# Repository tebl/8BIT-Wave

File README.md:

# 8BIT Wave
8BIT Wave is a project I started in order to build a digital cassette deck for my old 8-bit retro computers, my starting point was the schematic provided as part of the [DigiWavuino](https://github.com/rickyelqasem/DigiWavuino) project by Ricky ElQasem though it's more or less grown towards being its own thing since then. Later versions also support the [Maxduino](https://github.com/rcmolina/MaxDuino_v1.66)-firmware (includes tzxduino and arduitape functionality), that way I can use it with most - if not all of my vintage computers using one device (refer to maxduino documentation). Anyway, enough of all that - here is a picture of the device loading a game on ZX Spectrum:

One of my goals with the project has been to build the device I always wanted, the idea was to have something that looked like a cassette tape yet had all the functionality of maxduino and similar firmware. There is a firmware in the software-directory of this repository, but that was more a way of playing around with the Arduino without ever intending to finish it (it is only there in case someone wants to study and laugh at my cut-and-paste style of coding).

So my major contribution for this projection, to the world in general, is in the form of the three PCBs and some added amplifier options not found on any of the other open tzxduino clones I've looked at. The other goal, apart from looking cool was having a case without actually fixing my 3d-printer so for that reason the project also includes a backplate - this allows the user to avoid having to touch bare electronics when they handle it.

It is my belief that this project can be put together by anyone with moderate skills at soldering together components, but take care that you read through all of the documentation provided and not just start somewhere in the middle. All the components I've used are from chinese vendors such as AliExpress, banggood and ebay so the descriptions will reflect this (none of those sites have consistent part descriptions, so treat the parts list as general search terms and try to match them to pictures).

Further details will be available as part of the documentation for each of the [modules](#2-modules), see below for links.

## 1> Project status
There will always be things to do and polish, but at the current state it is an open design that can be used with the [MaxDuino](https://github.com/rcmolina/MaxDuino_v1.54). Note that different computers have that special sweet spot, so that you will need to do some tweaking in order to find what works best with your specific setup. 

## 2> Modules
The project has been split into several modules, these will be stacked together to a complete player. Faceplates and backplates can be considered optional, but normally you would only need one of each (some variants will be added later to match various displays so check out the description for each module before you commit).

| Module    |  | Order |
| --------- | ---------- | ----- |
| [8BitWave Module](https://github.com/tebl/8BIT-Wave/tree/master/8bitWave%20Module) | required | [PCBWay](https://www.pcbway.com/project/shareproject/8BitWave_Module.html) |
| [8BitWave Faceplate A1](https://github.com/tebl/8BIT-Wave/tree/master/8bitWave%20Faceplate%20A1) | optional | |
| [8BitWave Faceplate A2](https://github.com/tebl/8BIT-Wave/tree/master/8bitWave%20Faceplate%20A2) | recommended | [PCBWay](https://www.pcbway.com/project/shareproject/8BitWave_Faceplate.html) |
| [8BitWave Backplate](https://github.com/tebl/8BIT-Wave/tree/master/8bitWave%20Backplate) | optional | [PCBWay](https://www.pcbway.com/project/shareproject/8BitWave_Backplate.html) |

I'm using PCBway because I get a discount for every PCB ordered via them, so if you want to support this project then that is the way to do it. For other fabrication houses you would normally need to do is zip-up the contents of the export directory for each module and hand them those files (these are what is known as Gerber files). Note that the latest Gerber files may contain changes not yet tested by me, so if you want the ones I've tested then checkout my [PCBway shared projects](https://www.pcbway.com/project/shareproject/?tag=8BIT-Wave) relating to this project.

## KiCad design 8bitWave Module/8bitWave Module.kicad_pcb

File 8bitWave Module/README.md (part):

# 8BIT Wave Module

The 8BIT Wave module is the main heart of the project, it contains most of the active components found within the project. Building the module requires that you take some time to consider to which options you require, some in the case of the chosen amplifier are mutually exclusive and they both have their plusses and minuses. If you're still in the process of ordering components, skip to the BOM section of the document and start there - note that other modules such has the faceplate will have their documents detailing their construction and part specifications.

- 1> [Building the module](#1-building-the-module)
  - 1.1> [Installing common components](#11-installing-common-components)
  - 1.2> [Installing low-pass filter](#12-installing-low-pass-filter)
  - 1.3> [Installing amplifier](#13-installing-amplifier)
    - [1.3.1> LM386 amplifier option](#131-lm386-amplifier-option)
    - [1.3.2> GF1002 amplifier option](#132-gf1002-amplifier-option)
- 2> [Schematic](#2-schematic)
- 3> [BOM](#3-bom)
  - 3.1> [Common components](#31-common-components)
  - 3.2> [LM386 (amplifier)](#32-lm386-amplifier)
  - 3.3> [GF1002 (amplifier)](#33-gf1002-amplifier)
  - 3.4> [Low-pass filter](#34-low-pass-filter)

## 1> Building the module
So you've decided that you want the 8BIT Wave in your life, a bold choice and might I go so far as smile that someone took the time to build something I designed. The first step before breaking out the soldering iron, you can't use a glue-gun for this unless you do some extreme overclocking on the thing, is going through and ordering all the little bits you'll need. This should all be detailed inside the section later in this document, called the [BOM](#3-bom) (bill of manufacturing). Note that you will however have to make some decisions about a few of the options, mainly the amplification used and whether you want to install components for the low-pass filter. Read each section carefully before you commit to something, components are always harder to desolder than it is to solder them into place (when in doubt and have the extra PCB, just build another one - twice the solder fumes for just about the same price).

Got everything needed? Awesome. Break out your soldering iron, add some water to the sponge and start soldering at a reasonably controlled temperature. I have my iron set around 340 degrees Celsius, in Fahrenheit that would be too cold to accomplish much [cue laugh track]!

Continue by following sections [1.1](#11-installing-common-components) to install common common components, [1.2](#12-installing-low-pass-filter) to install a low-pass filter (if needed) and finally the amplifier option you require by following on in section [1.3](#13-installing-amplifier).

- [1.1> Installing common components](#11-installing-common-components)
- [1.2> Installing low-pass filter](#12-installing-low-pass-filter)
- [1.3> Installing amplifier](#13-installing-amplifier)

When all that is done, including any work that needs to be done on the faceplate/backplate you should now be able to put the entire thing together. What I recommend is that you get one of those M3 nylon hex standoff kits, that way you have a bunch available of various lengths that you can use while you build the completed solution. The ones I've between the faceplate and the main module are 12mm long, then whatever is the shortest I have available between backplate and the main module.

A minimum height build is shown below, here it is running Maxduino and the total height is around 26mm which is pretty good compared to most cased designs.

### 1.1> Installing common components
Solder parts specified in [common components](#31-common-components) into place, but take note that depending on the build you're going for you'll probably need to use some hex standoffs between this module and the faceplate - the ones I'm using is 12mm tall. You might get away with substituting the long pin headers with the regular ones if you opt to install the Arduino directly without anything in between, but doing so requires you to do some dry-fitting along the way to make sure nothing becomes too short (a long pin can be cut, a short one can be heated and pushed a bit through to make up for it).

The modules that can be installed directly on the board is shown above, both of them usually come with pin headers already attached - we'll deal with those along the way. The display you can probably put aside as you've most likely opted for installing it on one of my beautiful faceplates instead (I can't blame you, that was really what this project was all about). If you however do not want the faceplate (why though?), make sure you install the display as the last thing you ever do - otherwise you'll have problems installing components below it (add some electrical tape between the modules to avoid accidentally shorting things).

The MicroSD Card Adapter will come with right-angle header attached to it, just straighten them using some pliers. Add some double-sided tape to the top of the MicroSD-slot, turn it upside down and solder it into place on the module.

### 1.2> Installing low-pass filter
Solder in the parts for the [low-pass filter](#34-low-pass-filter), unless you know you'll need them. They have been shown to make programs easier to load on the MSX-line of computers though it's the only place I think it is needed. If you chose to skip the installation, feel free to install a wire-link across J5 pins 1-2. With the filter installed, add some dual-row header pins to J5 - disable the filter by placing a jumper across pins 1-2 as before. When enabling the feature you'll need to remove this jumper, instead add jumpers across pins 3-4 and 5-6. 

### 1.3> Installing amplifier
With this step out of the way, we're ready to install one of the amplifier options, the easiest one is simply using the module without an amplifier - install jumpers across J7 pins 1-2 as well as 11-12 to use the output directly (this will also allow you to bypass an installed amplifier). The following sections assume that you've chosen to install either LM386 or GF1002 amplifier, they operate at different voltages and should not be installed in the same system.

- [1.3.1> LM386 amplifier option](#131-lm386-amplifier-option)
- [1.3.2> GF1002 amplifier option](#132-gf1002-amplifier-option)

#### 1.3.1 LM386 amplifier option
Using the classic LM386 amplifier is more or less the goto choice for any amateur hardware tinkerer, thinking mostly about me here - you're probably awesome so don't worry about it! It is also a common option found on other tzxduino boards, but note that the module really requires 9v to function properly with a few vintage systems, even just specific revisions may require this as opposed to the 5v provided by the Arduino.

Try it out, it might work perfectly at 5v too so you need to try out which works best for the systems you have. If you explicitly don't want to add a 9v power supply into the mix, the [GF1002 amplifier](#132-gf1002-amplifier-option) is a different option that has been designed to operate at 5v.

Still here? 9v center positive power supply it is then. Install components specified in the [BOM](#32-lm386-amplifier). Link pins JP6 pins 2-3 and make a checkmark in the 9v checkbox on the back of the module, this is here so you don't accidentally connect the wrong voltage to the module. Note that with JP6 in the wrong position, this will more than likely fry most of the components on the board - do it right or watch it burn (probably a lot less spectacular than that)! Refer to the picture below if in doubt.

Most components can be installed as shown, but in order to keep the spacing between the module and faceplate as little as possible (12mm by my count) you'll need to install some of the components on their side - the capactitors especially can be tall, by putting them on the side you have a bit more room to work with. The same goes for the volume control, this is the same 10k bourns 3296w potentiometer most usually have in their parts bin - what I've done is simply mount it on the side by bending the pins. It is then anchored to the board by using some leftover wire-cuttings from one of the LEDs.

As mentioned before, J7 configures the amplification used by the system. You can use jumper pins 1-2 to bypass the LM386 if needed, but since you're here you probably want to enable the thing - this is done by adding jumpers across 5-6 instead (assuming you still have a jumper in place across pins 11-12).

#### 1.3.2 GF1002 amplifier option
The GF1002 amplifier module, based on PAM8403 module, is a stereo amplifier that's been designed for use with 5v (LM386 requires 9v) power sources so it is a good match for the *8BIT Wave*. For the most part it is easy to install, but feel free to refer to section [3.3](#33-gf1002-amplifier) for a list of parts needed and install them as you see fit - a picture of the completed module can be seen below.

The most important thing to remember when installing it is that the audio jacks must be in place before you attempt to install the GF1002, mainly because they will be partially covered by the module. You will also need to have the module in part recessed into the cutout on the PCB, this was done so that the overall thickness of all the PCBs can be kept to a minimum. Use long pin headers, break them into sections and use those when soldering it in at the correct height - ideally it'll be resting comfortably on top of the 3.5mm audio jack.

Power can also be supplied directly by plugging in a 5v DC (center positive) power supply into the barrel connector, this require JP6 to have a wire-ling across pins 1-2. These components are listed as optional (in parenthesis), so make a checkmark in the corresponding box on the back of the module board to mark it as such.

As mentioned before, J7 configures the amplification used by the system. You can use jumper pins 1-2 to bypass the GF1002 if needed, but since you're here you probably want to enable the thing - this is done by adding jumpers across J7 pins 7-8 as well as pins 9-10. Note that no other J7 pins should be jumpered here, the GF1002 needs to have it's own ground and shorting it using pins 11-12 will cause it to overheat and shut down.

# 2> Schematic
The supplied KiCad files should be sufficient as both a schematic and as a  starting point for ordering PCBs (basically you could just zip the contents of the export folder and upload that on a fabrication site), the schematic is also available in [PDF-format](https://github.com/tebl/8BIT-Wave/tree/master/documentation/schematic) found within the schematics-part of the [documentation](https://github.com/tebl/8BIT-Wave/tree/master/documentation).

# 3> BOM
Most parts should be easy to get a hold of from your favourite local electronic component shop, but given that I don't have access to such shops where I live so everything was based on whatever I could get cheapest from eBay/AliExpress (free shipping, plan on waiting 3-4 weeks for delivery though).

As described in the section *building the module*, the BOM will also need to be divided into various sections depending on the chosen build - these difference between these is the choice of amplifier installed. Common components are needed for all of them, refer to the rest for a different choice - do note however that the option of no amplification similar to what is found on the tzxduino compact is also an option. Components listen in parenthesis is to be considered optional, some of them will be obsolete when using a faceplate (only one display needed).

# 3.1> Common components
These are the components that will be required on all variants of the 8BIT Wave, do note that depending on options chosen the design may be simplified by doing part substitutions. In particular the long pin can be substituted by ordinary pin headers if all components are soldered directly to the PCB without using sockets, LM386 or no amplifier etc. Refer to the following [picture](https://github.com/tebl/8BIT-Wave/raw/master/gallery/2020-02-22%2000.55.06.jpg) if you're wondering what the MicroSD Card Adapter module looks like.

| Reference    | Item                                                 | Count |
| ------------ | ---------------------------------------------------- | ----- |
| PCB          | Fabricate using Gerber files                         |     1 |
| A1           | Arduino Nano or Every                                |     1 |
| A2           | MicroSD Card Adapter for Arduino                     |     1 |
| C10          | 100uF 16V electrolytic capacitor                     |     1 |
| D1,D2 **     | 5mm LED                                              |    (2)|
| IC1          | SSD1306 I2C OLED 128x64 (0.96")                      |    (1)|
| J1           | PJ-210 2.5mm audio socket                            |    (1)|
| J2           | PJ-307 3.5mm audio socket (5 pin)                    |     1 |
| J6,JP5       | 3 pin straight header (long pins)                    |     2 |
| J3           | 7 pin header (long pins)                             |     1 |
| J5 *         | 2x3 straight pin header                              |     1 |
| J7           | 2x7 straight dual row pin header                     |     1 |
| R6,R7 **     | 330 Ohm resistor                                     |    (2)|
| R8,R9 ***    | 4k7 (4700) Ohm resistor                              |    (2)|
| SW1-SW5      | 6x6x5mm right-angle momentary button                 |     5 |
| Jumpers      | Pin header jumper caps                               |     5 |

*) This is used to enable/disable the low-pass filter, if you don't need or want to install the components listed in section 3.4 you can just install a wire link across pins 1-2 to permanently bypass it.

**) These components are only on the 8BIT-Wave, the Maxduino firmware does not support them so they are listed as optional.

***) These are I2C pull-ups, these are normally needed as the OLED-displays tend to already come with those installed there. Only install if you've verified that this is the issue.

# 3.2> LM386 (amplifier)
The classic option for amplifying the audio signal on a tzxduino. No amplification at all is also an option that can be considered, but with some systems and even revisions of specific systems there will be different audio requirements that will require active amplification (see 3.3 for a different option).

Note that the LM386 really needs more than 5v to function properly, so you'll need to power the system with a 9v DC (center positive) using the barrel connector. This requires JP6 to have a wire-link between pins 2-3, pins 1-2 should only be linked if you mean to use a different amplification option and a 5v DC (center positive) power supply. Make a checkmark on the 9v section on the back of the board.

| Reference    | Item                                                 | Count |
| ------------ | ---------------------------------------------------- | ----- |
| C5           | 100nF ceramic capacitor (5mm)                        |     1 |
| C6,C8        | 10uF 16V electrolytic capacitor                      |     2 |
| C7           | 100uF 16V electrolytic capacitor                     |     1 |
| C9           | 47nF ceramic capacitor (5mm)                         |     1 |
| C11          | 220uF 16V electrolytic capacitor                     |     1 |
| D3           | 1n4001 diode (DO-41)                                 |     1 |
| J4           | 5.5mm x 2.1mm barrel connector (PCB mount)           |     1 |
| R5           | 10 Ohm resistor                                      |     1 |
| RV2          | Bourns 3296W 10k ohm potentiometer                   |     1 |
| JP1,JP6      | 3 pin straight header with jumper                    |     2 |
| JP4          | 2 pin straight header with jumper                    |     1 |

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
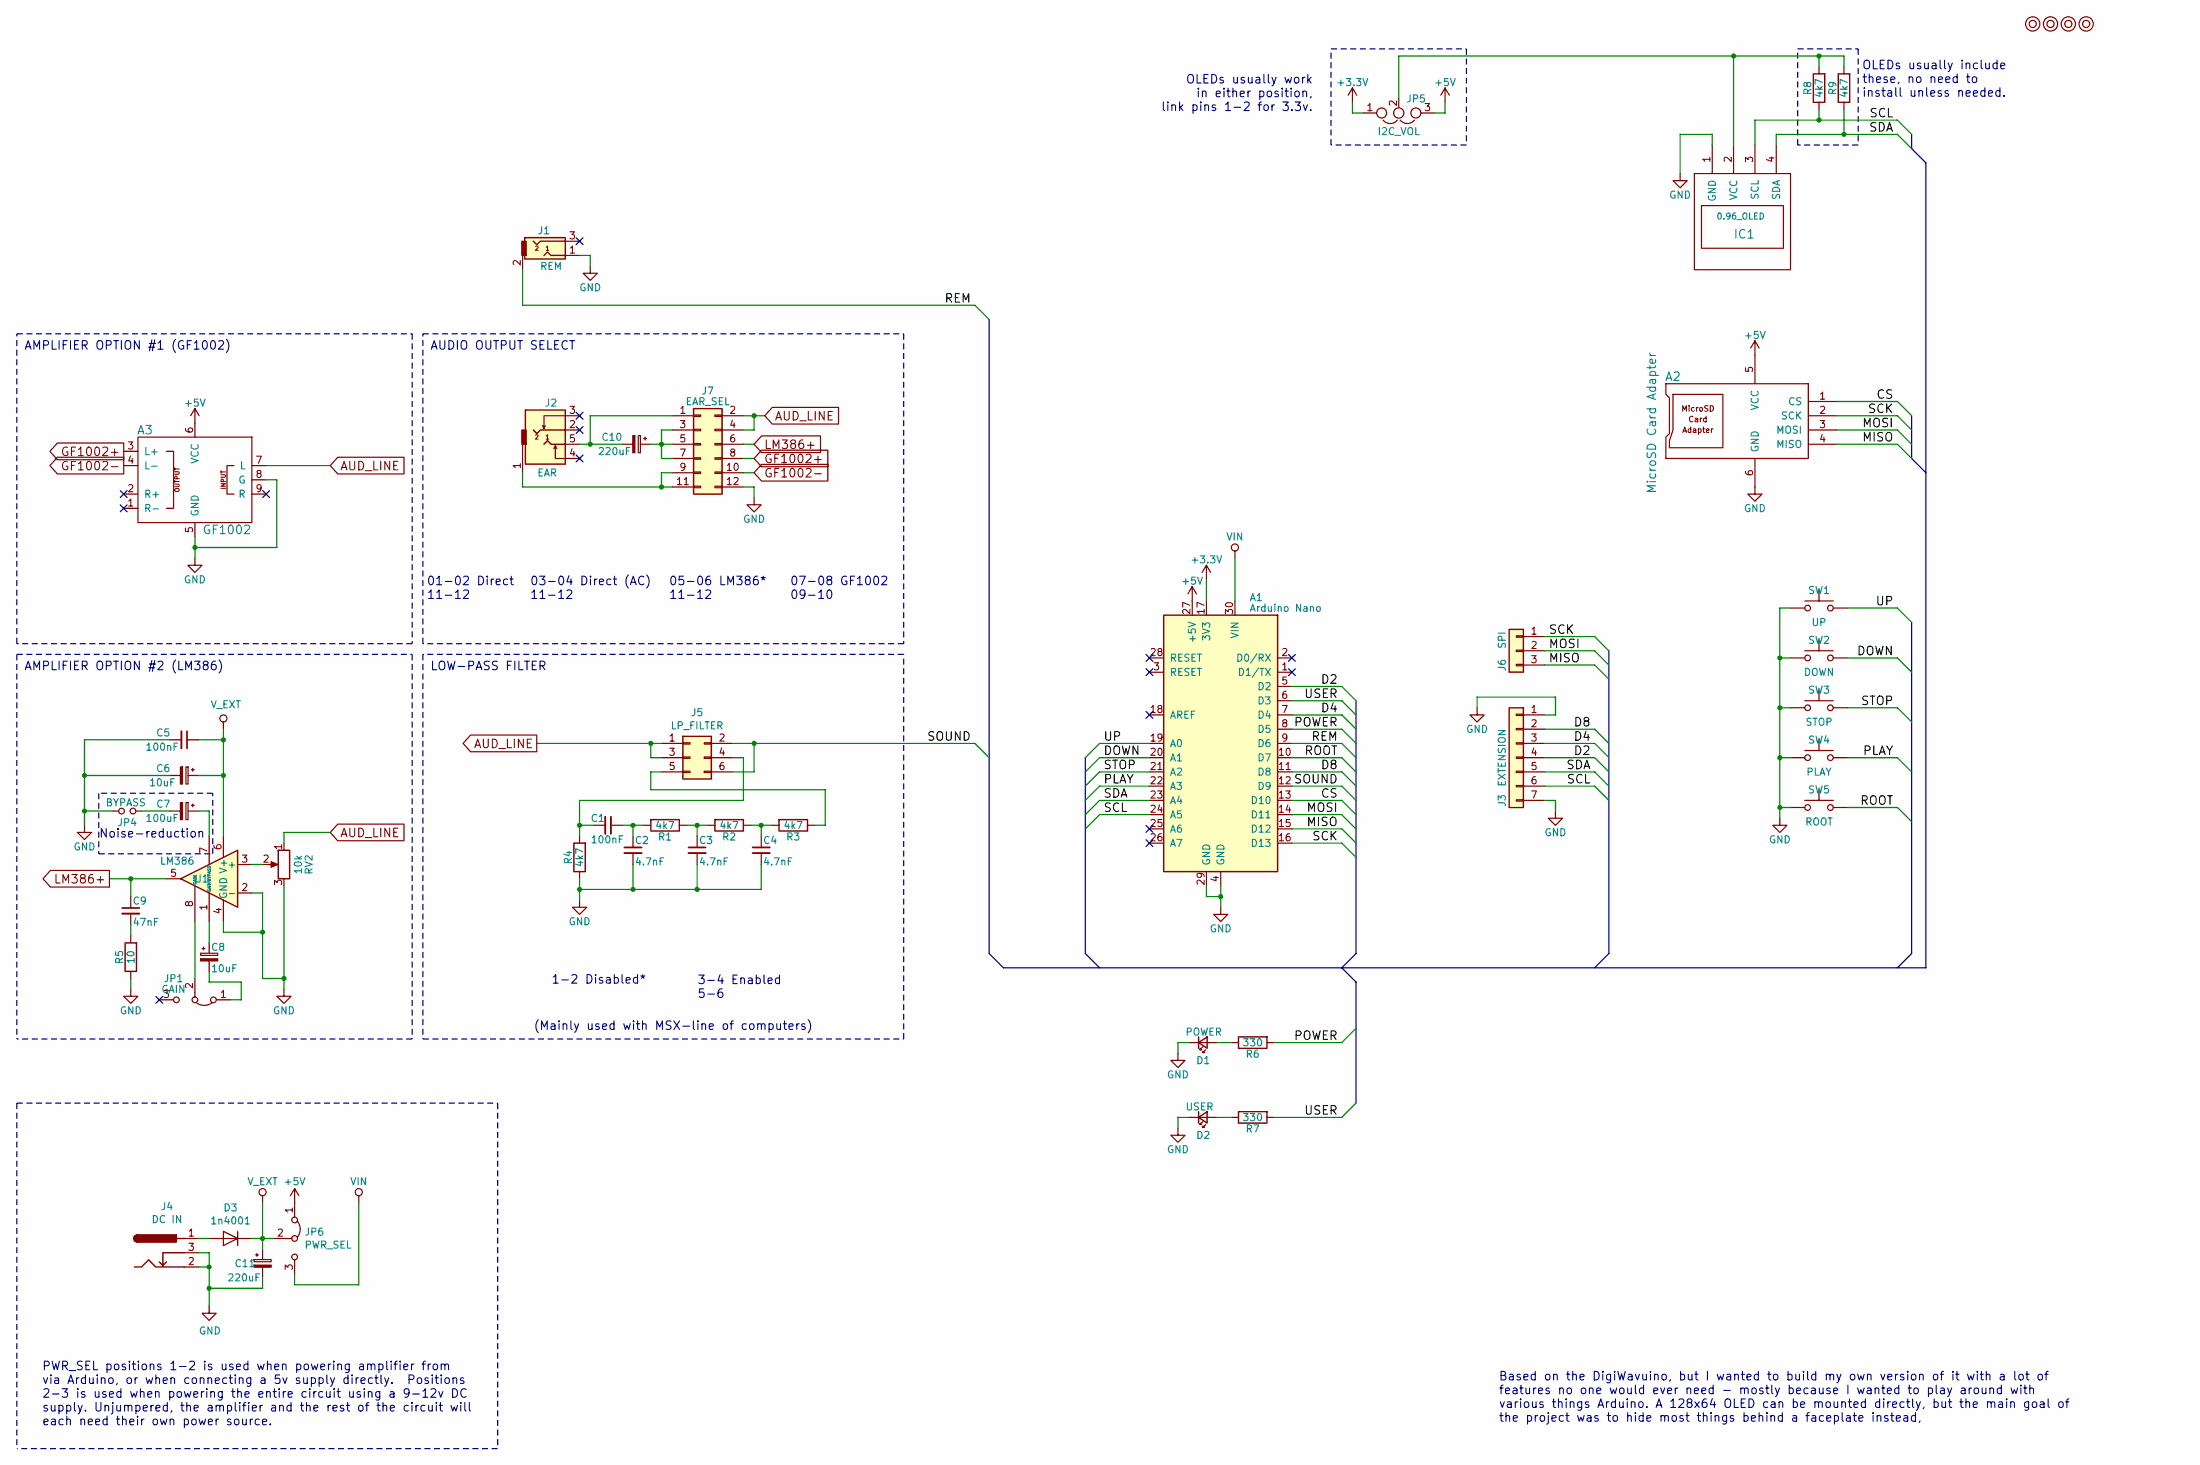
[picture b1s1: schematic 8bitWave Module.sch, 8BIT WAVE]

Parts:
A1: Arduino Nano; Arduino_Nano
A2: MicroSD Card Adapter; MicroSD_Card_Adapter
A3: GF1002; GF1002_reverse
C1, C5: 100nF; C_Disc_D4.7mm_W2.5mm_P5.00mm
C2, C3, C4: 4.7nF; C_Disc_D4.7mm_W2.5mm_P5.00mm
C6, C8: 10uF; CP_Radial_D4.0mm_P2.00mm
C7: 100uF; CP_Radial_D5.0mm_P2.00mm
C9: 47nF; C_Disc_D4.7mm_W2.5mm_P5.00mm
C10: 220uF; CP_Radial_D5.0mm_P2.50mm
C11: 220uF; CP_Radial_D6.3mm_P2.50mm
D1: POWER; LED_D5.0mm
D2: USER; LED_D5.0mm
D3: 1n4001; D_DO-41_SOD81_P10.16mm_Horizontal
IC1: 0.96_OLED; 0.96_I2C_OLED
J1: REM; 2.5mm_audio
J2: EAR; Tayda_3.5mm_stereo_TRS_jack_A-853
J3: EXTENSION; Pin_Header_Straight_1x07_Pitch2.54mm
J4: DC IN; BARREL_JACK
J5: LP_FILTER; Pin_Header_Straight_2x03_Pitch2.54mm
J6: SPI; Pin_Header_Straight_1x03_Pitch2.54mm
J7: EAR_SEL; Pin_Header_Straight_2x06_Pitch2.54mm
JP1: GAIN; Pin_Header_Straight_1x03_Pitch2.54mm
JP4: BYPASS; Pin_Header_Straight_1x02_Pitch2.54mm
JP5: I2C_VOL; Pin_Header_Straight_1x03_Pitch2.54mm
JP6: PWR_SEL; Pin_Header_Straight_1x03_Pitch2.54mm
M1, M2, M3, M4: Mounting; M3
R1, R2, R3, R4, R8, R9: 4k7; R_Axial_DIN0207_L6.3mm_D2.5mm_P10.16mm_Horizontal
R5: 10; R_Axial_DIN0207_L6.3mm_D2.5mm_P10.16mm_Horizontal
R6, R7: 330; R_Axial_DIN0207_L6.3mm_D2.5mm_P10.16mm_Horizontal
RV2: 10k; Potentiometer_Trimmer_Bourns_3296W
SW1: UP; SW_Tactile_SPST_Angled_PTS645Vx39-2LFS
SW2: DOWN; SW_Tactile_SPST_Angled_PTS645Vx39-2LFS
SW3: STOP; SW_Tactile_SPST_Angled_PTS645Vx39-2LFS
SW4: PLAY; SW_Tactile_SPST_Angled_PTS645Vx39-2LFS
SW5: ROOT; SW_Tactile_SPST_Angled_PTS645Vx39-2LFS
U1: LM386; DIP-8_W7.62mm_Socket_LongPads

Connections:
+3V3: A1.17 (3V3), JP5.1
+5V: A1.27 (+5V), A2.5 (VCC), A3.6 (VCC), JP5.3, JP6.1 (A)
/CS: A1.13 (D10), A2.1 (CS)
/D2: A1.5 (D2), J3.4
/D4: A1.7 (D4), J3.3
/D8: A1.11 (D8), J3.2
/DOWN: A1.20 (A1), SW2.1
/MISO: A1.15 (D12), A2.4 (MISO), J6.3
/MOSI: A1.14 (D11), A2.3 (MOSI), J6.2
/PLAY: A1.22 (A3), SW4.1
/POWER: A1.8 (D5), R6.2
/REM: A1.9 (D6), J1.2
/ROOT: A1.10 (D7), SW5.1
/SCK: A1.16 (D13), A2.2 (SCK), J6.1
/SCL: A1.24 (A5), IC1.3 (SCL), J3.6, R8.1
/SDA: A1.23 (A4), IC1.4 (SDA), J3.5, R9.1
/SOUND: A1.12 (D9), J5.2, J5.6
/STOP: A1.21 (A2), SW3.1
/UP: A1.19 (A0), SW1.1
/USER: A1.6 (D3), R7.2
AUD_LINE: A3.7 (L), J5.1, J5.3, J7.2, J7.4, RV2.1
GF1002+: A3.3 (L+), J7.8
GF1002-: A3.4 (L-), J7.10
GND: A1.4 (GND), A1.29 (GND), A2.6 (GND), A3.5 (GND), A3.8 (G), C2.2, C3.2, C4.2, C5.2, C6.2, C11.2, D1.1 (K), D2.1 (K), IC1.1 (GND), J1.1, J3.1, J3.7, J4.2, J4.3, J7.12, JP4.2, R4.1, R5.1, RV2.3, SW1.2, SW2.2, SW3.2, SW4.2, SW5.2, U1.2 (-), U1.4 (GND)
LM386+: C9.1, J7.6, U1.5
unnamed: C1.1, C2.1, R1.2
unnamed: C1.2, J5.4, R4.2
unnamed: C3.1, R1.1, R2.2
unnamed: C4.1, R2.1, R3.2
unnamed: C7.1, U1.7 (BYPASS)
unnamed: C7.2, JP4.1
unnamed: C8.1, U1.1 (GAIN)
unnamed: C8.2, JP1.1 (A)
unnamed: C9.2, R5.2
unnamed: C10.1, J7.3, J7.5, J7.7
unnamed: C10.2, J2.5, J7.1
unnamed: D1.2 (A), R6.1
unnamed: D2.2 (A), R7.1
unnamed: D3.2 (A), J4.1
unnamed: IC1.2 (VCC), JP5.2, R8.2, R9.2
unnamed: J2.1, J7.9, J7.11
unnamed: J5.5, R3.1
unnamed: JP1.2 (C), U1.8 (GAIN)
unnamed: RV2.2, U1.3 (+)
VEXT: C5.1, C6.1, C11.1, D3.1 (K), JP6.2 (C), U1.6 (V+)
VIN: A1.30 (VIN), JP6.3 (B)

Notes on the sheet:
Noise-reduction
OLEDs usually include these, no need to install unless needed.
OLEDs usually work in either position, link pins 1-2 for 3.3v.
Based on the DigiWavuino, but I wanted to build my own version of it with a lot of features no one would ever need - mostly because I wanted to play around with various things Arduino. A 128x64 OLED can be mounted directly, but the main goal of the project was to hide most things behind a faceplate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
PWR_SEL positions 1-2 is used when powering amplifier from via Arduino, or when connecting a 5v supply directly. Positions 2-3 is used when powering the entire circuit using a 9-12v DC supply. Unjumpered, the amplifier and the rest of the circuit will each need their own power source.
LOW-PASS FILTER
1-2 Disabled*
3-4 Enabled 5-6
(Mainly used with MSX-line of computers)
01-02 Direct 11-12
03-04 Direct (AC) 11-12
05-06 LM386* 11-12
07-08 GF1002 09-10
AMPLIFIER OPTION #2 (LM386)
AMPLIFIER OPTION #1 (GF1002)
AUDIO OUTPUT SELECT

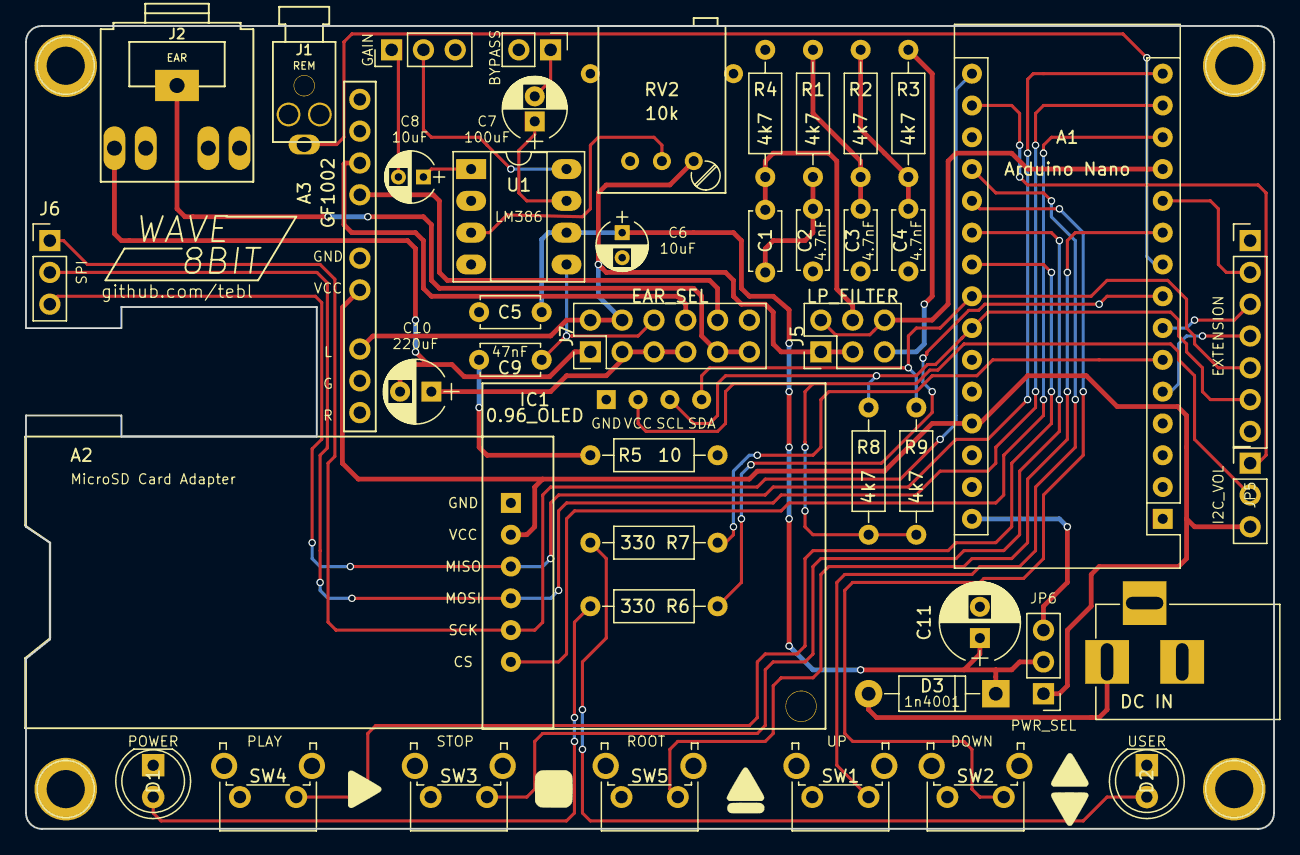
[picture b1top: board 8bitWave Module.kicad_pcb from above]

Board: 2 copper layers, 99.7 x 64.1 mm, 49 parts (0 on the bottom side), 46 nets.

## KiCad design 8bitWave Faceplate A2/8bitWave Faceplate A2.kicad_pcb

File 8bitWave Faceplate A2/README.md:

# 8BIT Wave Faceplate A2

The faceplate is mainly what separates the *8BIT Wave* from all other tzxduino clones, it makes it *really really cool* (to quote a really really cool comedy about male supermodels)! You could actually do without the thing entirely as the OLED-display could potentially be installed on the main module instead, but what would the fun be in building a unit that'd be less than what it could be. The difference between A1 and A2 is that A2 doesn't include a bunch of extra SMD components, mostly there because I wanted to practice on soldering those (in doubt, get the A2 variant).

## 1> Building the module

Start by checking out the [BOM](#3-bom) and verify that you have the components needed before continuing, it's beyond frustrating to realize you need just that single item before being able to complete the build - with shipping times from China as they are, better to get it right the first time (if it's very cheap I tend to order several just in case one gets delayed somewhere).

Before building the faceplate you need to first determine which variation of the 128x64 SSD1306 OLED-display (0.96") you actually have, there is the **original** one used by this faceplate - the newer variation is slightly smaller and incompatible with this PCB as the mounting is different. Refer to the picture below when ordering, one giveaway is that the newer variation have a narrower ribbon cable at the bottom.

The actual display usually comes with pin headers already installed, which is unfortunate as they are on the wrong side - refer to the pictures below to see how it is meant to fit into the mounting. You could always try desoldering the pins, but I've found that this is a rather cumbersome step - even with the suitable tools available to me. The easiest solution however is to melt the solder on a single pin using your soldering iron, then pushing the pin through the PCB using something metal like a pair of pliers (remember: hot metal burns - a lot).

Align the pins with the front of the PCB and solder it in place. Use M2 nylon screws and nuts to affix the bottom, this keeps people from accidentally pushing the display into the case. On the back of the faceplate, there are two solder connections that need to be made - JP1 and JP2. These need to be shorted according to the order of pins used on the OLED-display, solder accross *1-2* if the first one is marked **GND**. Pins *2-3* if it is marked **VCC**.

As the last step, solder into place the female pin headers on the underside of the faceplate - like pictured. There are extra pads on one of them, this is just there because I wanted it to be symmetrical (*I KNOW*). Theoretically you could install extra long pin headers here and solder it directly to the module under, but that is only recommended when building several units at once and the components being used have been verified.

Earlier revisions have pads for SMD LEDs that can be lit up using a couple of shift registers, I've not included these in the BOM as this is features not supported in any of the firmwares available. I might remove them entirely at a later point in order to keep everything through-hole components.

# 2> Schematic
The supplied KiCad files should be sufficient as both a schematic and as a  starting point for ordering PCBs (basically you could just zip the contents of the export folder and upload that on a fabrication site), the schematic is also available in [PDF-format](https://github.com/tebl/8BIT-Wave/tree/master/documentation/schematic) found within the schematics-part of the [documentation](https://github.com/tebl/8BIT-Wave/tree/master/documentation).

# 3> BOM
Most parts should be easy to get a hold of from your favourite local electronic component shop, but given that I don't have access to such shops where I live so everything was based on whatever I could get cheapest from eBay/AliExpress (free shipping, plan on waiting 3-4 weeks for delivery though).

| Reference    | Item                                                 | Count |
| ------------ | ---------------------------------------------------- | ----- |
| PCB          | Fabricate using Gerber files                         |    (1)|
| IC1          | SSD1306 I2C OLED 128x64 (0.96") (**"Original"**)     |    (1)|
| J1 *         | Female 3 pin header                                  |     1 |
| J2           | Female 10 pin header                                 |    (1)|
| J3 *         | Female 7 pin header                                  |     1 |

*) J1 and J3 are placed right next to eachother, so you could just install a female 10 pin header here. That'll also reduce number of parts needed by one, if that matters.

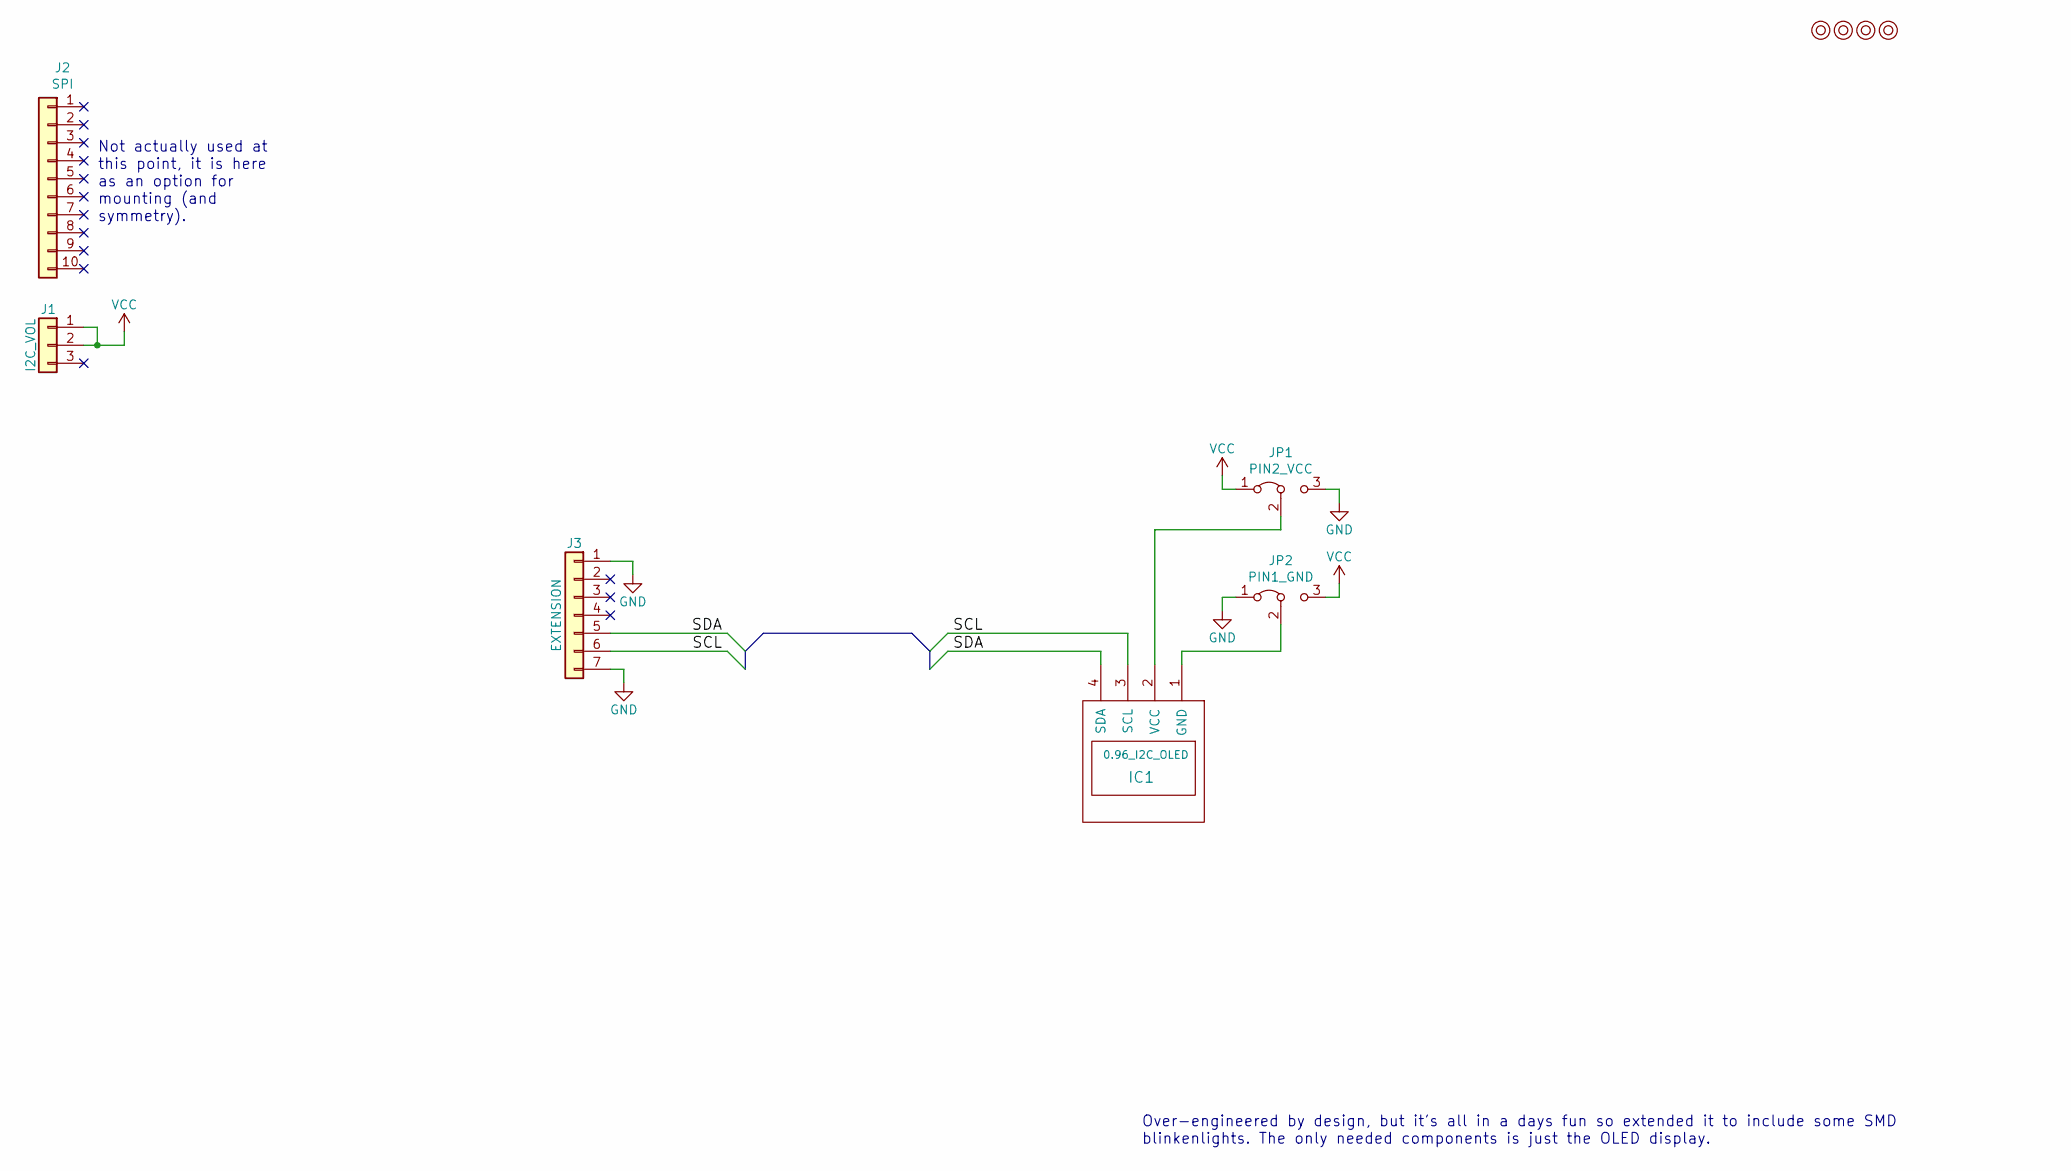
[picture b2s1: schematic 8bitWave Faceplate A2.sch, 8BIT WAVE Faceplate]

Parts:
IC1: 0.96_I2C_OLED; 0.96_I2C_OLED2
J1: I2C_VOL; Pin_Header_Straight_1x03_Pitch2.54mm
J2: SPI; Pin_Header_Straight_1x10_Pitch2.54mm
J3: EXTENSION; Pin_Header_Straight_1x07_Pitch2.54mm
JP1: PIN2_VCC; OLED_SEL
JP2: PIN1_GND; OLED_SEL
M1, M2, M3, M4: Mounting; M3

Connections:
/SCL: IC1.3 (SCL), J3.6
/SDA: IC1.4 (SDA), J3.5
GND: J3.1, J3.7, JP1.3 (B), JP2.1 (A)
unnamed: IC1.1 (GND), JP2.2 (C)
unnamed: IC1.2 (VCC), JP1.2 (C)
VCC: J1.1, J1.2, JP1.1 (A), JP2.3 (B)

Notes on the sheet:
Over-engineered by design, but it's all in a days fun so extended it to include some SMD blinkenlights. The only needed components is just the OLED display.
Not actually used at this point, it is here as an option for mounting (and symmetry).

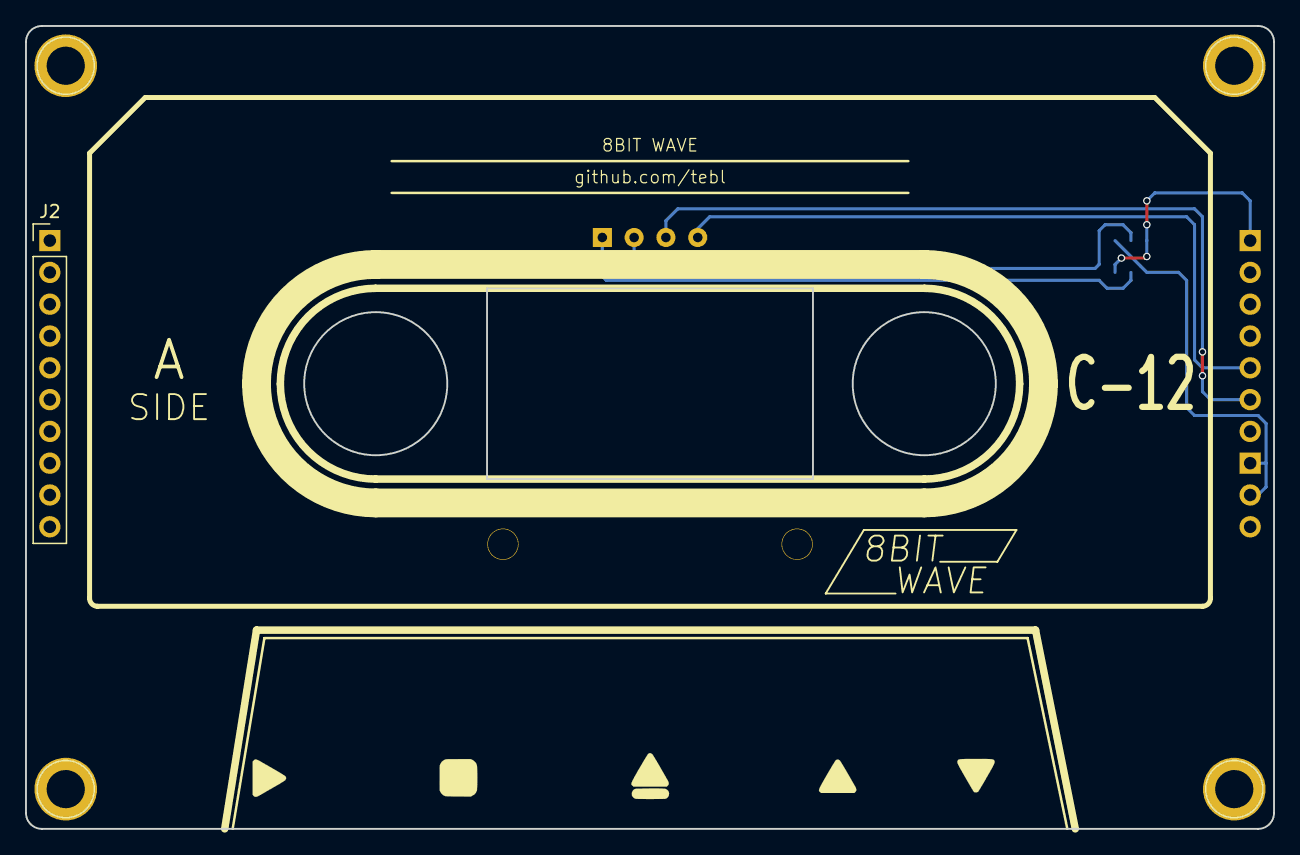
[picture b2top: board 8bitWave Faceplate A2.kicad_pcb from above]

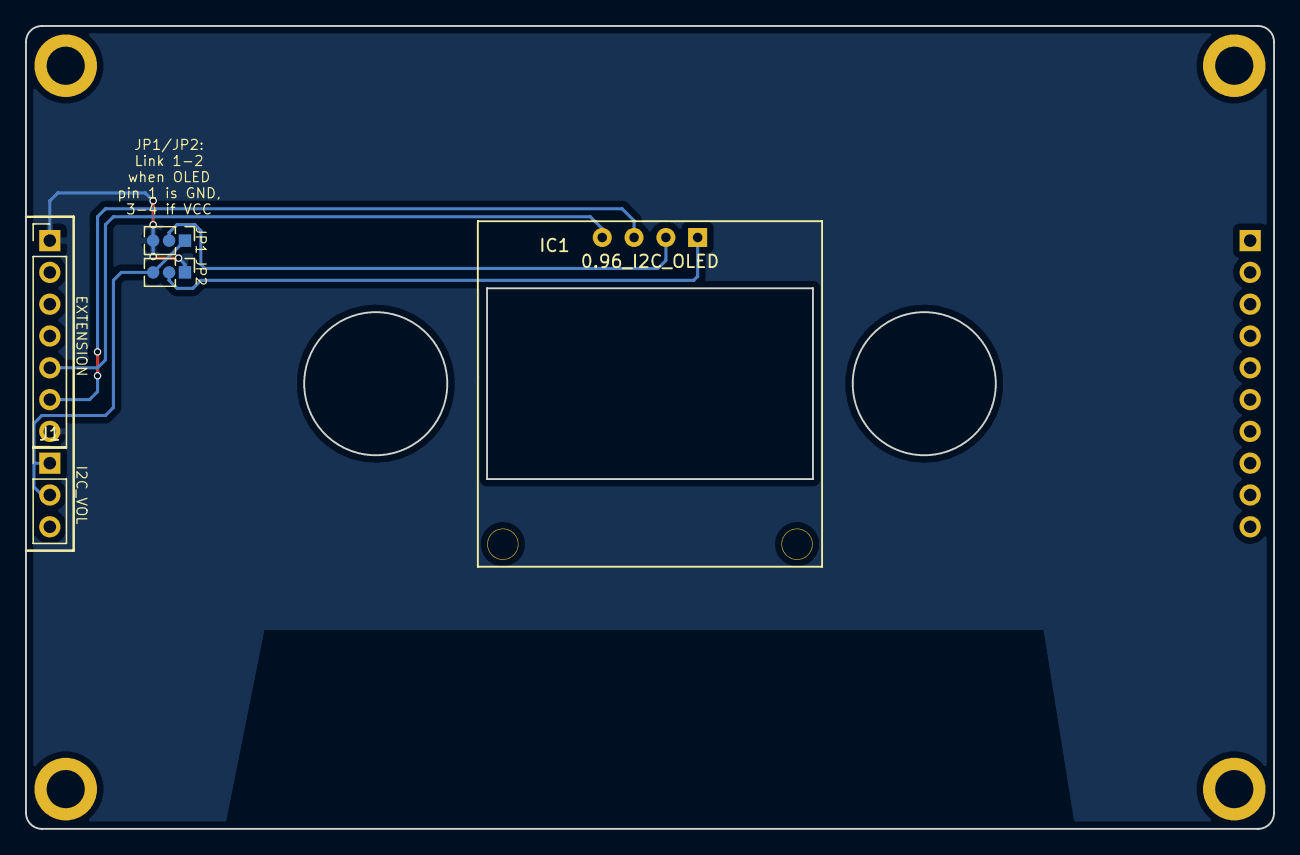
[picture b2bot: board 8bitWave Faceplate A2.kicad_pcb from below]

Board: 2 copper layers, 99.7 x 64.1 mm, 10 parts (4 on the bottom side), 6 nets.

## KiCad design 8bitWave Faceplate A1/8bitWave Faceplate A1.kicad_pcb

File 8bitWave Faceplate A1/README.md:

# 8BIT Wave Faceplate A1

The faceplate is mainly what separates the *8BIT Wave* from all other tzxduino clones, it makes it *really really cool* (to quote a really really cool comedy about male supermodels)! You could actually do without the thing entirely as the OLED-display could potentially be installed on the main module instead, but what would the fun be in building a unit that'd be less than what it could be.

## 1> Building the module

Start by checking out the [BOM](#3-bom) and verify that you have the components needed before continuing, it's beyond frustrating to realize you need just that single item before being able to complete the build - with shipping times from China as they are, better to get it right the first time (if it's very cheap I tend to order several just in case one gets delayed somewhere).

Before building the faceplate you need to first determine which variation of the 128x64 SSD1306 OLED-display (0.96") you actually have, there is the **original** one used by this faceplate - the newer variation is slightly smaller and incompatible with this PCB as the mounting is different. Refer to the picture below when ordering, one giveaway is that the newer variation have a narrower ribbon cable at the bottom.

The actual display usually comes with pin headers already installed, which is unfortunate as they are on the wrong side - refer to the pictures below to see how it is meant to fit into the mounting. You could always try desoldering the pins, but I've found that this is a rather cumbersome step - even with the suitable tools available to me. The easiest solution however is to melt the solder on a single pin using your soldering iron, then pushing the pin through the PCB using something metal like a pair of pliers (remember: hot metal burns - a lot).

Align the pins with the front of the PCB and solder it in place. Use M2 nylon screws and nuts to affix the bottom, this keeps people from accidentally pushing the display into the case. On the back of the faceplate, there are two solder connections that need to be made - JP1 and JP2. These need to be shorted according to the order of pins used on the OLED-display, solder accross *1-2* if the first one is marked **GND**. Pins *2-3* if it is marked **VCC**.

As the last step, solder into place the female pin headers on the underside of the faceplate - like pictured. There are extra pads on one of them, this is just there because I wanted it to be symmetrical (*I KNOW*). Theoretically you could install extra long pin headers here and solder it directly to the module under, but that is only recommended when building several units at once and the components being used have been verified.

Earlier revisions have pads for SMD LEDs that can be lit up using a couple of shift registers, I've not included these in the BOM as this is features not supported in any of the firmwares available. I might remove them entirely at a later point in order to keep everything through-hole components.

# 2> Schematic
The supplied KiCad files should be sufficient as both a schematic and as a  starting point for ordering PCBs (basically you could just zip the contents of the export folder and upload that on a fabrication site), the schematic is also available in [PDF-format](https://github.com/tebl/8BIT-Wave/tree/master/documentation/schematic) found within the schematics-part of the [documentation](https://github.com/tebl/8BIT-Wave/tree/master/documentation).

# 3> BOM
Most parts should be easy to get a hold of from your favourite local electronic component shop, but given that I don't have access to such shops where I live so everything was based on whatever I could get cheapest from eBay/AliExpress (free shipping, plan on waiting 3-4 weeks for delivery though).

| Reference    | Item                                                 | Count |
| ------------ | ---------------------------------------------------- | ----- |
| PCB          | Fabricate using Gerber files                         |    (1)|
| IC1          | SSD1306 I2C OLED 128x64 (0.96") (**"Original"**)     |    (1)|
| J1 *         | Female 3 pin header                                  |     1 |
| J2           | Female 10 pin header                                 |    (1)|
| J3 *         | Female 7 pin header                                  |     1 |

*) J1 and J3 are placed right next to eachother, so you could just install a female 10 pin header here. That'll also reduce number of parts needed by one, if that matters.

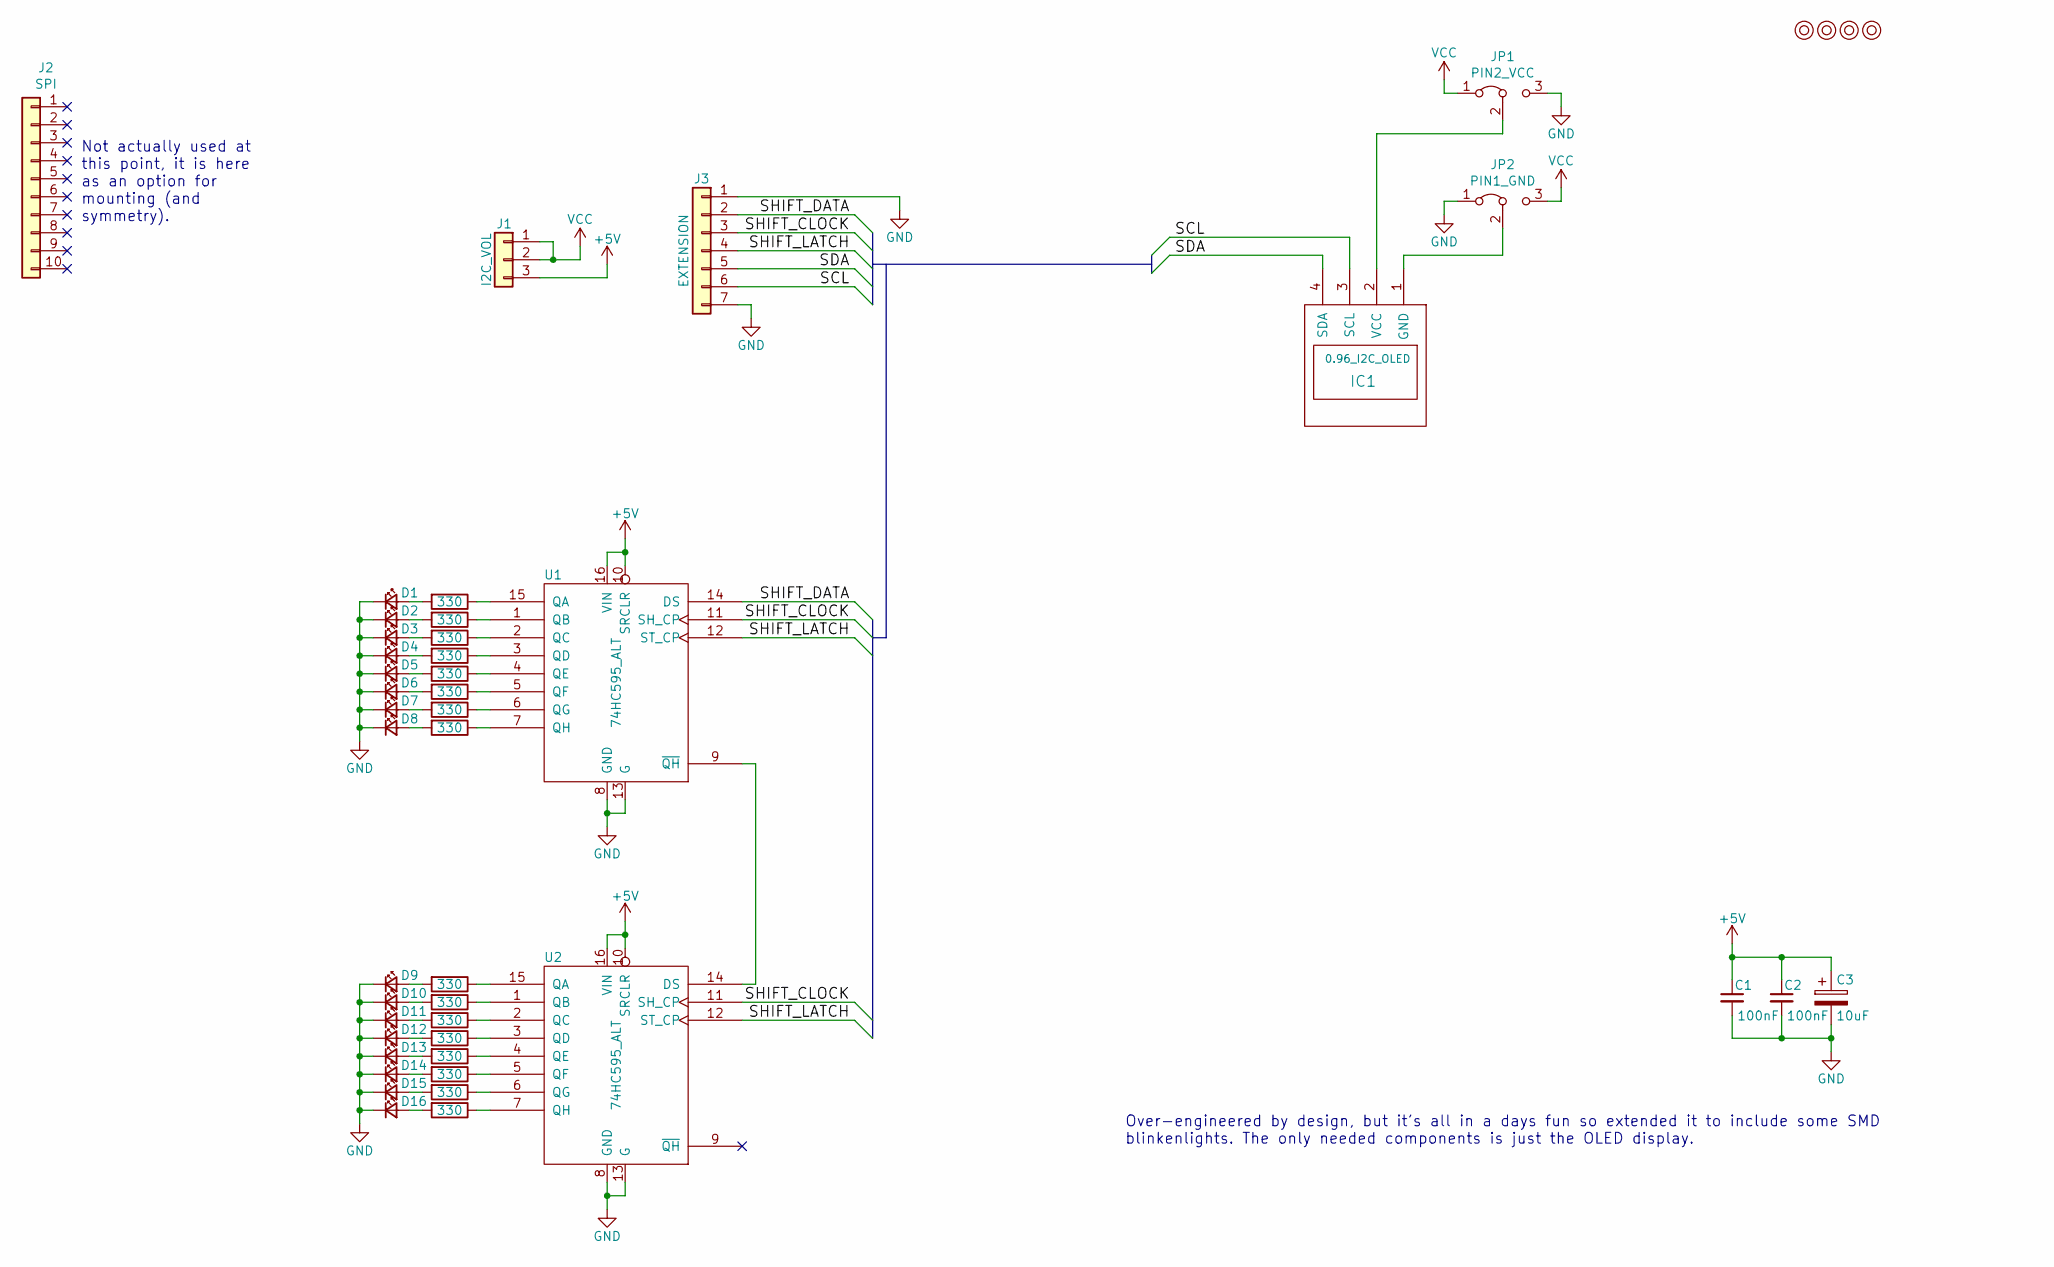
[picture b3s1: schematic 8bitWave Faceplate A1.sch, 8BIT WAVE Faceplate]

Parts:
C1, C2: 100nF; C_0805_HandSoldering
C3: 10uF; CP_Elec_6.3x5.3
D1, D2, D3, D4, D5, D6, D7, D8, D9, D10, D11, D12, D13, D14, D15, D16: RED; LED_0805_HandSoldering
IC1: 0.96_I2C_OLED; 0.96_I2C_OLED2
J1: I2C_VOL; Pin_Header_Straight_1x03_Pitch2.54mm
J2: SPI; Pin_Header_Straight_1x10_Pitch2.54mm
J3: EXTENSION; Pin_Header_Straight_1x07_Pitch2.54mm
JP1: PIN2_VCC; OLED_SEL
JP2: PIN1_GND; OLED_SEL
M1, M2, M3, M4: Mounting; M3
R1, R2, R3, R4, R5, R6, R7, R8, R9, R10, R11, R12, R13, R14, R15, R16: 330; R_0805_HandSoldering
U1, U2: 74HC595_ALT; SO-16-N

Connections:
+5V: C1.1, C2.1, C3.1, J1.3, U1.10 (SRCLR), U1.16 (VIN), U2.10 (SRCLR), U2.16 (VIN)
/SCL: IC1.3 (SCL), J3.6
/SDA: IC1.4 (SDA), J3.5
/SHIFT_CLOCK: J3.3, U1.11 (SH_CP), U2.11 (SH_CP)
/SHIFT_DATA: J3.2, U1.14 (DS)
/SHIFT_LATCH: J3.4, U1.12 (ST_CP), U2.12 (ST_CP)
GND: C1.2, C2.2, C3.2, D1.1 (K), D2.1 (K), D3.1 (K), D4.1 (K), D5.1 (K), D6.1 (K), D7.1 (K), D8.1 (K), D9.1 (K), D10.1 (K), D11.1 (K), D12.1 (K), D13.1 (K), D14.1 (K), D15.1 (K), D16.1 (K), J3.1, J3.7, JP1.3 (B), JP2.1 (A), U1.8 (GND), U1.13 (G), U2.8 (GND), U2.13 (G)
unnamed: D1.2 (A), R1.2
unnamed: D2.2 (A), R2.2
unnamed: D3.2 (A), R3.2
unnamed: D4.2 (A), R4.2
unnamed: D5.2 (A), R5.2
unnamed: D6.2 (A), R6.2
unnamed: D7.2 (A), R7.2
unnamed: D8.2 (A), R8.2
unnamed: D9.2 (A), R9.2
unnamed: D10.2 (A), R10.2
unnamed: D11.2 (A), R11.2
unnamed: D12.2 (A), R12.2
unnamed: D13.2 (A), R13.2
unnamed: D14.2 (A), R14.2
unnamed: D15.2 (A), R15.2
unnamed: D16.2 (A), R16.2
unnamed: IC1.1 (GND), JP2.2 (C)
unnamed: IC1.2 (VCC), JP1.2 (C)
unnamed: R1.1, U1.15 (QA)
unnamed: R2.1, U1.1 (QB)
unnamed: R3.1, U1.2 (QC)
unnamed: R4.1, U1.3 (QD)
unnamed: R5.1, U1.4 (QE)
unnamed: R6.1, U1.5 (QF)
unnamed: R7.1, U1.6 (QG)
unnamed: R8.1, U1.7 (QH)
unnamed: R9.1, U2.15 (QA)
unnamed: R10.1, U2.1 (QB)
unnamed: R11.1, U2.2 (QC)
unnamed: R12.1, U2.3 (QD)
unnamed: R13.1, U2.4 (QE)
unnamed: R14.1, U2.5 (QF)
unnamed: R15.1, U2.6 (QG)
unnamed: R16.1, U2.7 (QH)
unnamed: U1.9 (~QH), U2.14 (DS)
VCC: J1.1, J1.2, JP1.1 (A), JP2.3 (B)

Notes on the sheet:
Over-engineered by design, but it's all in a days fun so extended it to include some SMD blinkenlights. The only needed components is just the OLED display.
Not actually used at this point, it is here as an option for mounting (and symmetry).
